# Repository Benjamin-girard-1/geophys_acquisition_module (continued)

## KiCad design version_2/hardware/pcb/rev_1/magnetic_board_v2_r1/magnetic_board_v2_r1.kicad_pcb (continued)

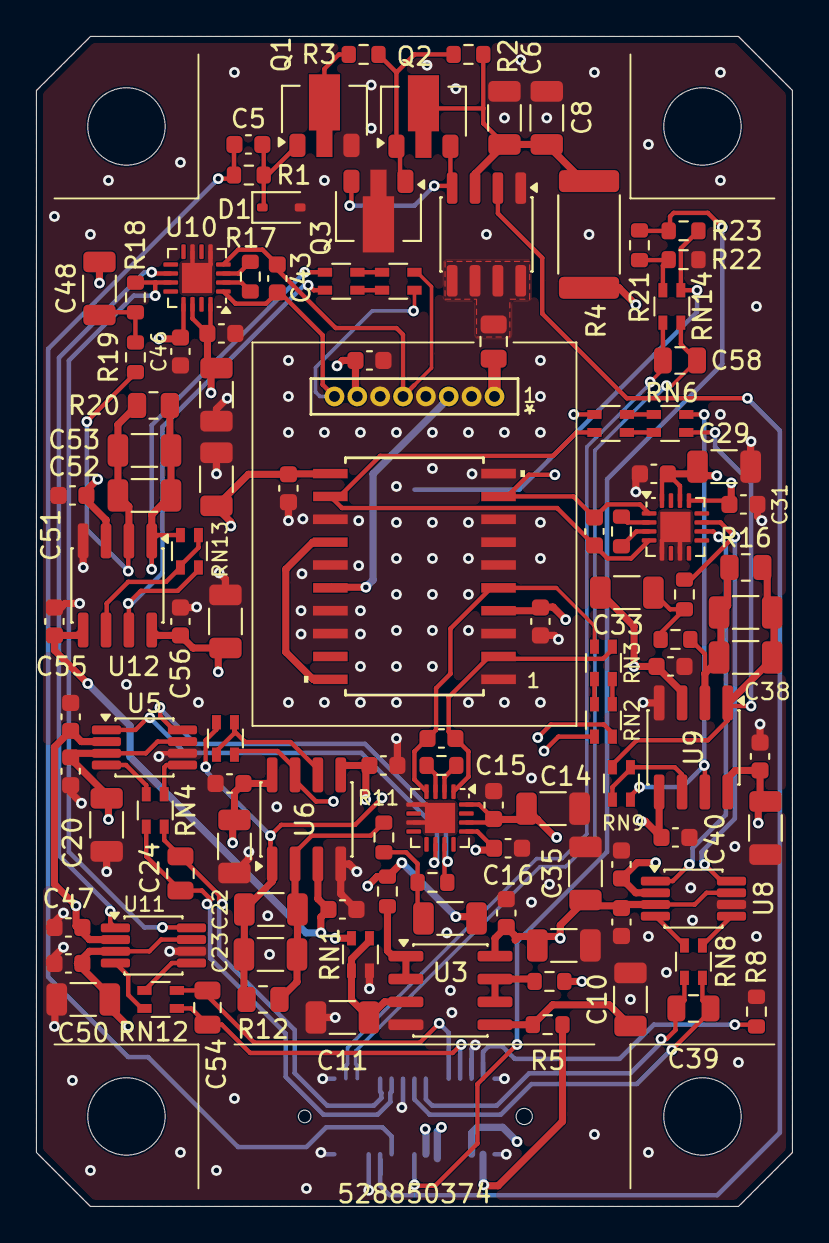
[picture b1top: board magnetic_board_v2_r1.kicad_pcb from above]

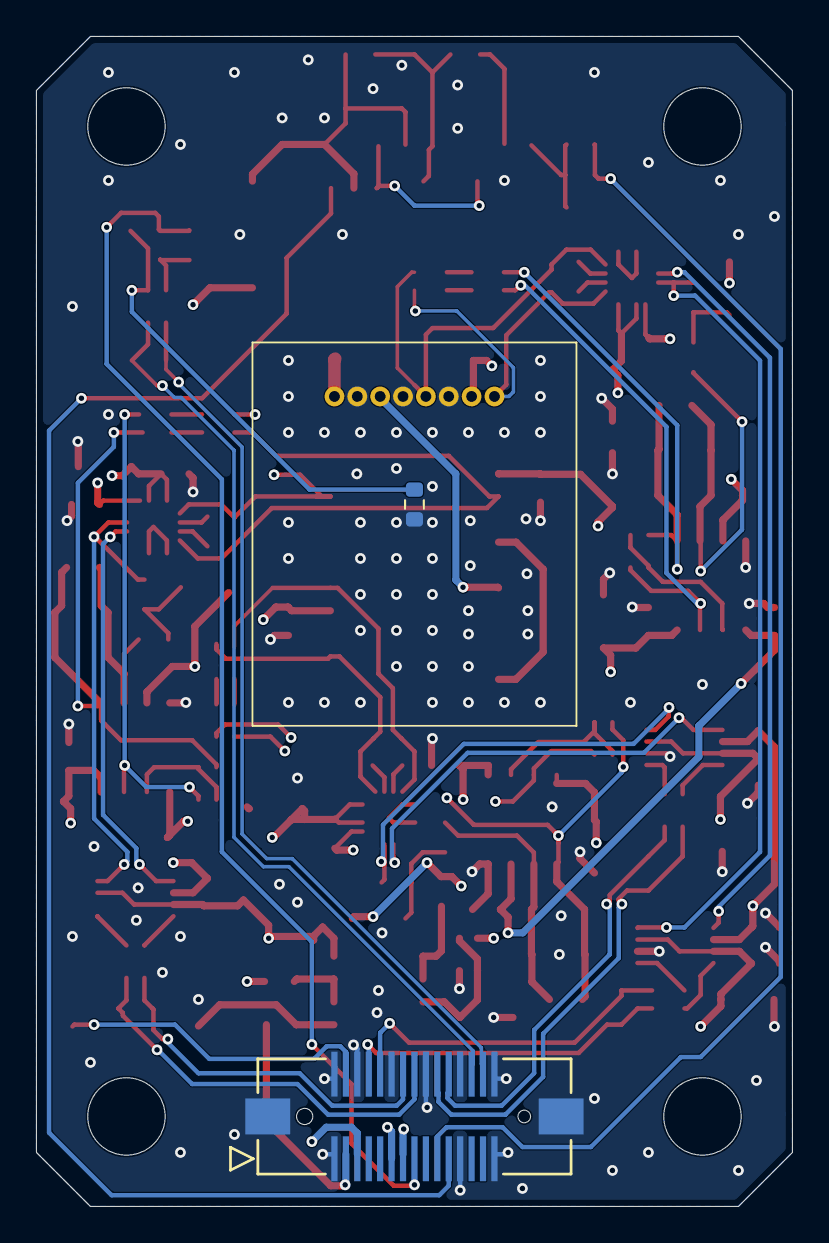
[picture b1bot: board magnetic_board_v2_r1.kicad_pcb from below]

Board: 4 copper layers, 42.0 x 65.0 mm, 118 parts (2 on the bottom side), 79 nets.

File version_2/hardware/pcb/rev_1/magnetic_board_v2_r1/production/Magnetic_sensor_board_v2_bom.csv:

Designator,Footprint,Quantity,Value,LCSC Part #
"C1, C6, C8",1206,3,10u,C13585
"C10, C11, C12, C14, C20, C22, C23, C27, C29, C35, C37, C38, C42, C44, C50, C52, C53, C57",1206,18,4u7,C29823
"C13, C28, C43",0603,3,10n,C57112
"C15, C16, C17, C19, C2, C21, C25, C26, C3, C30, C31, C32, C34, C36, C4, C40, C41, C45, C46, C47, C49, C51, C55, C56, C9",0603,25,100n,C14663
"C18, C33, C48",1206,3,47u,C96123
"C24, C39, C54, C58, C7",0805,5,220n,C5378
C5,0603,1,1n,C1588
D1,D_SOD-323,1,1N4148WS,C2128
"Q1, Q2",SOT-89-3,2,D882,C9634
Q3,SOT-89-3,1,B772,C24278
Q4,SO-8_3.9x4.9mm_P1.27mm,1,DMC3028LSD,C460874
"R1, R2, R3, R5",0603,4,1k,C21190
"R10, R14, R18",0603,3,300k,C5948140
"R11, R15, R19, R8",0603,4,20k,C2076520
"R12, R16, R20",0805,3,100M,C169373
"R13, R17, R9",0603,3,120,C860088
"R21, R22, R23",0603,3,100k,C860056
R4,2512,1,220,C4202072
"R6, R7",0603,2,20,C22950
RN1,R_Array_Convex_2x0603,1,10k,C2654064
"RN10, RN11, RN13, RN2, RN3, RN5, RN6, RN7, RN9",R_Array_Convex_2x0603,9,20k,C5553154
"RN12, RN14, RN4, RN8",R_Array_Convex_2x0603,4,1k,C1731140
"U10, U4, U7",VQFN-16-1EP_3x3mm_P0.5mm_EP1.68x1.68mm,3,INA851RGTR,C5371575
"U11, U5, U8",VSSOP-8_3x3mm_P0.65mm,3,THP210DGK,C976185
"U12, U3, U6, U9",SOIC-8_3.9x4.9mm_P1.27mm,4,OPA2197xD,C139363

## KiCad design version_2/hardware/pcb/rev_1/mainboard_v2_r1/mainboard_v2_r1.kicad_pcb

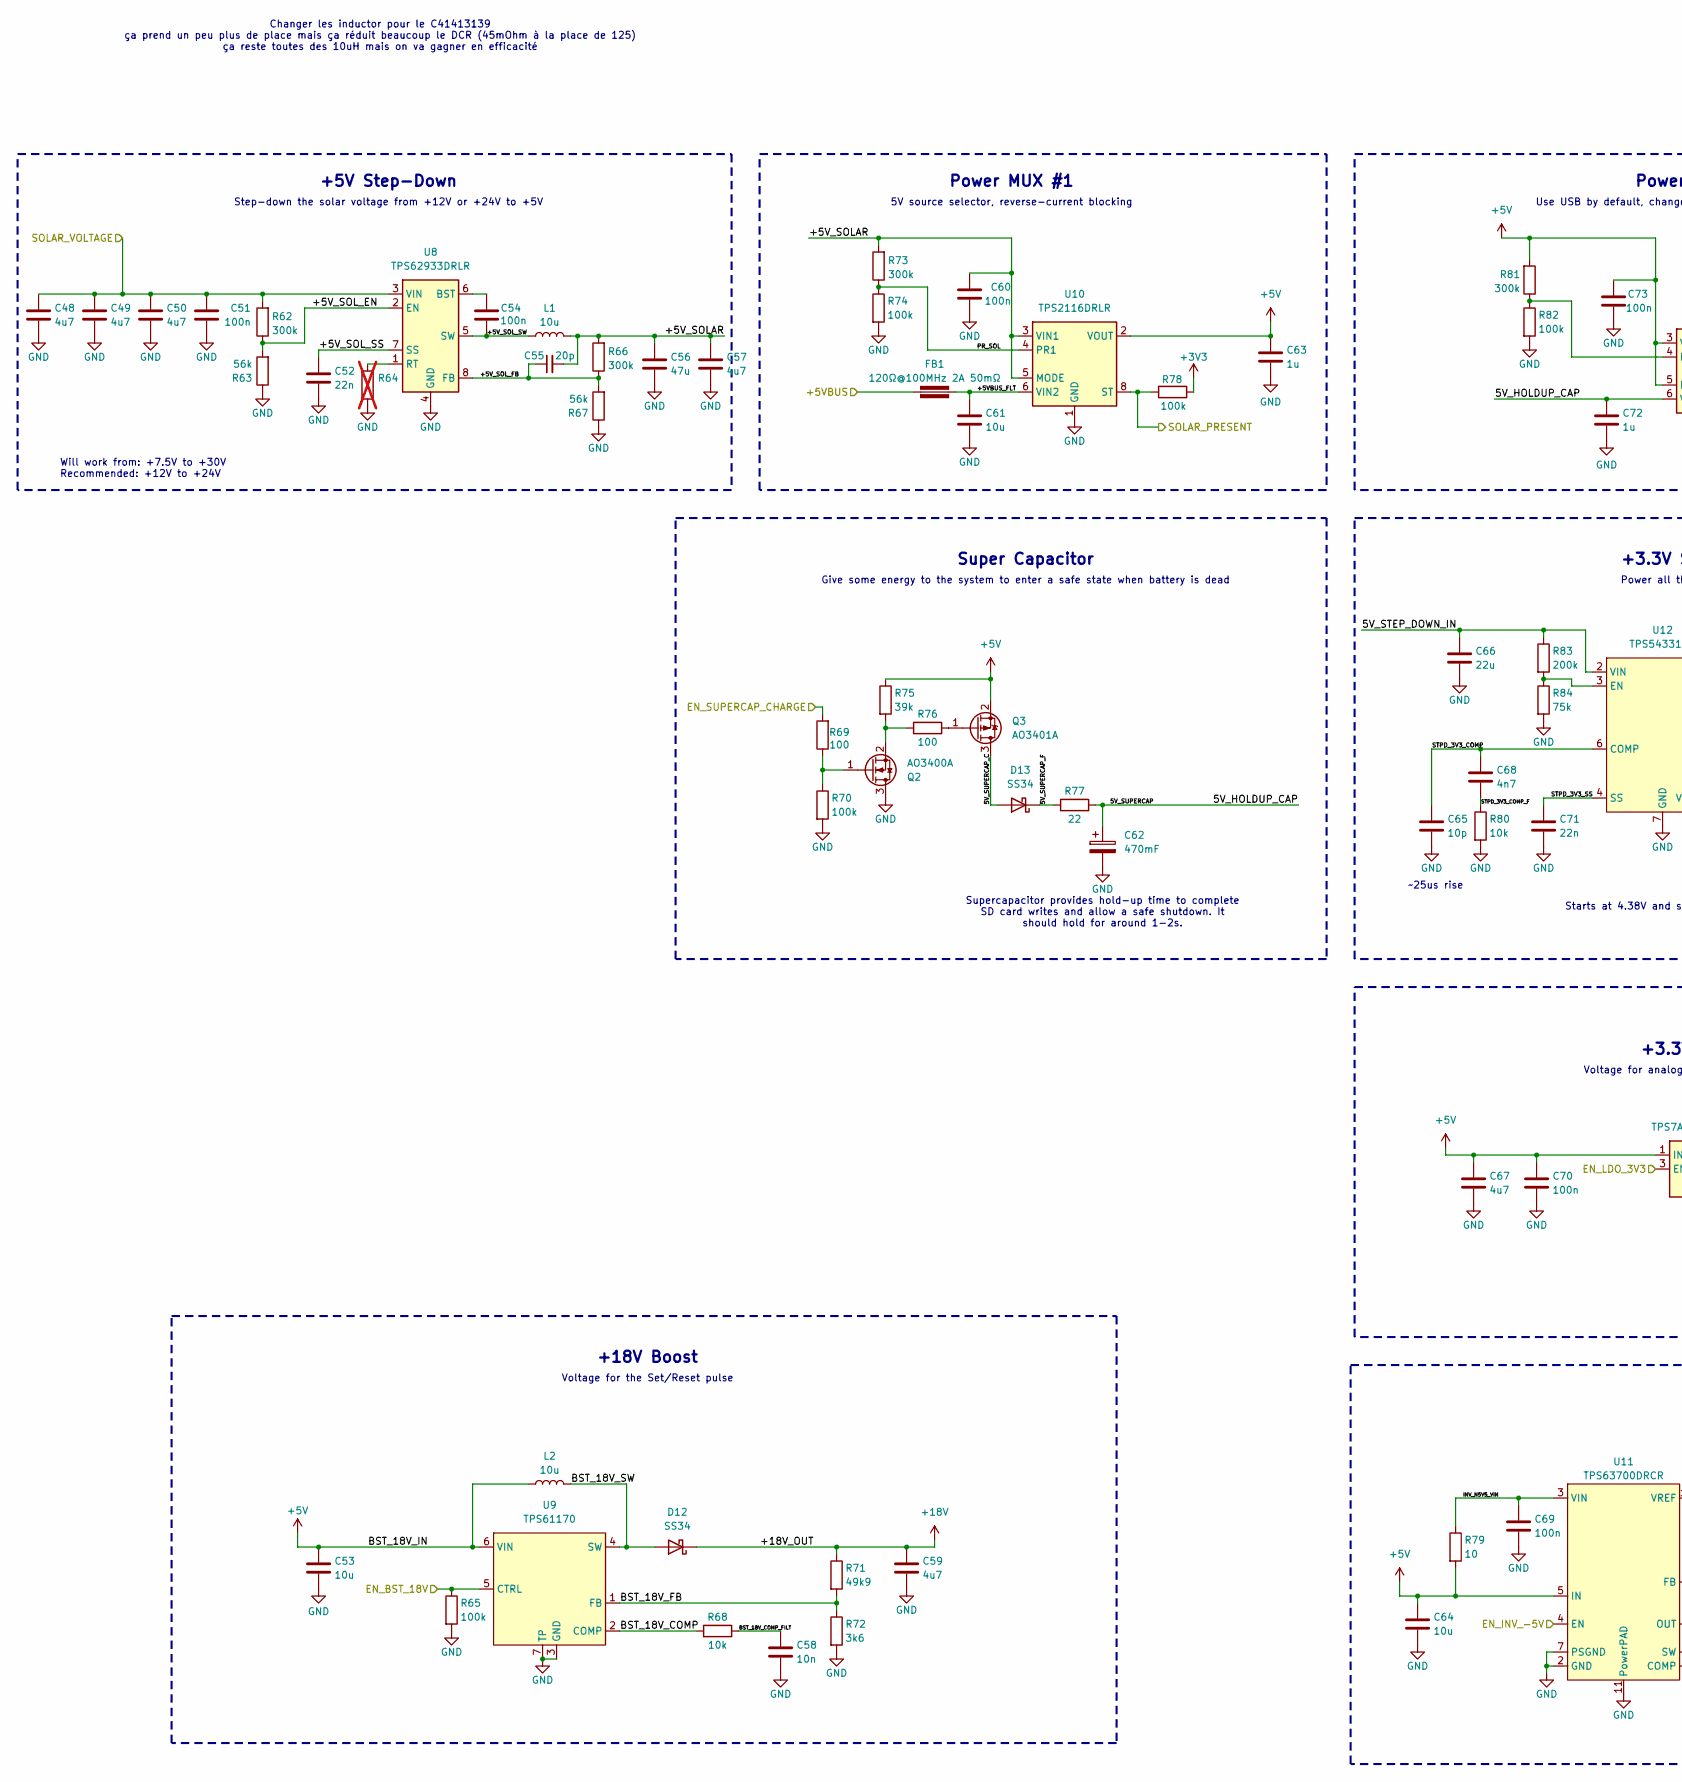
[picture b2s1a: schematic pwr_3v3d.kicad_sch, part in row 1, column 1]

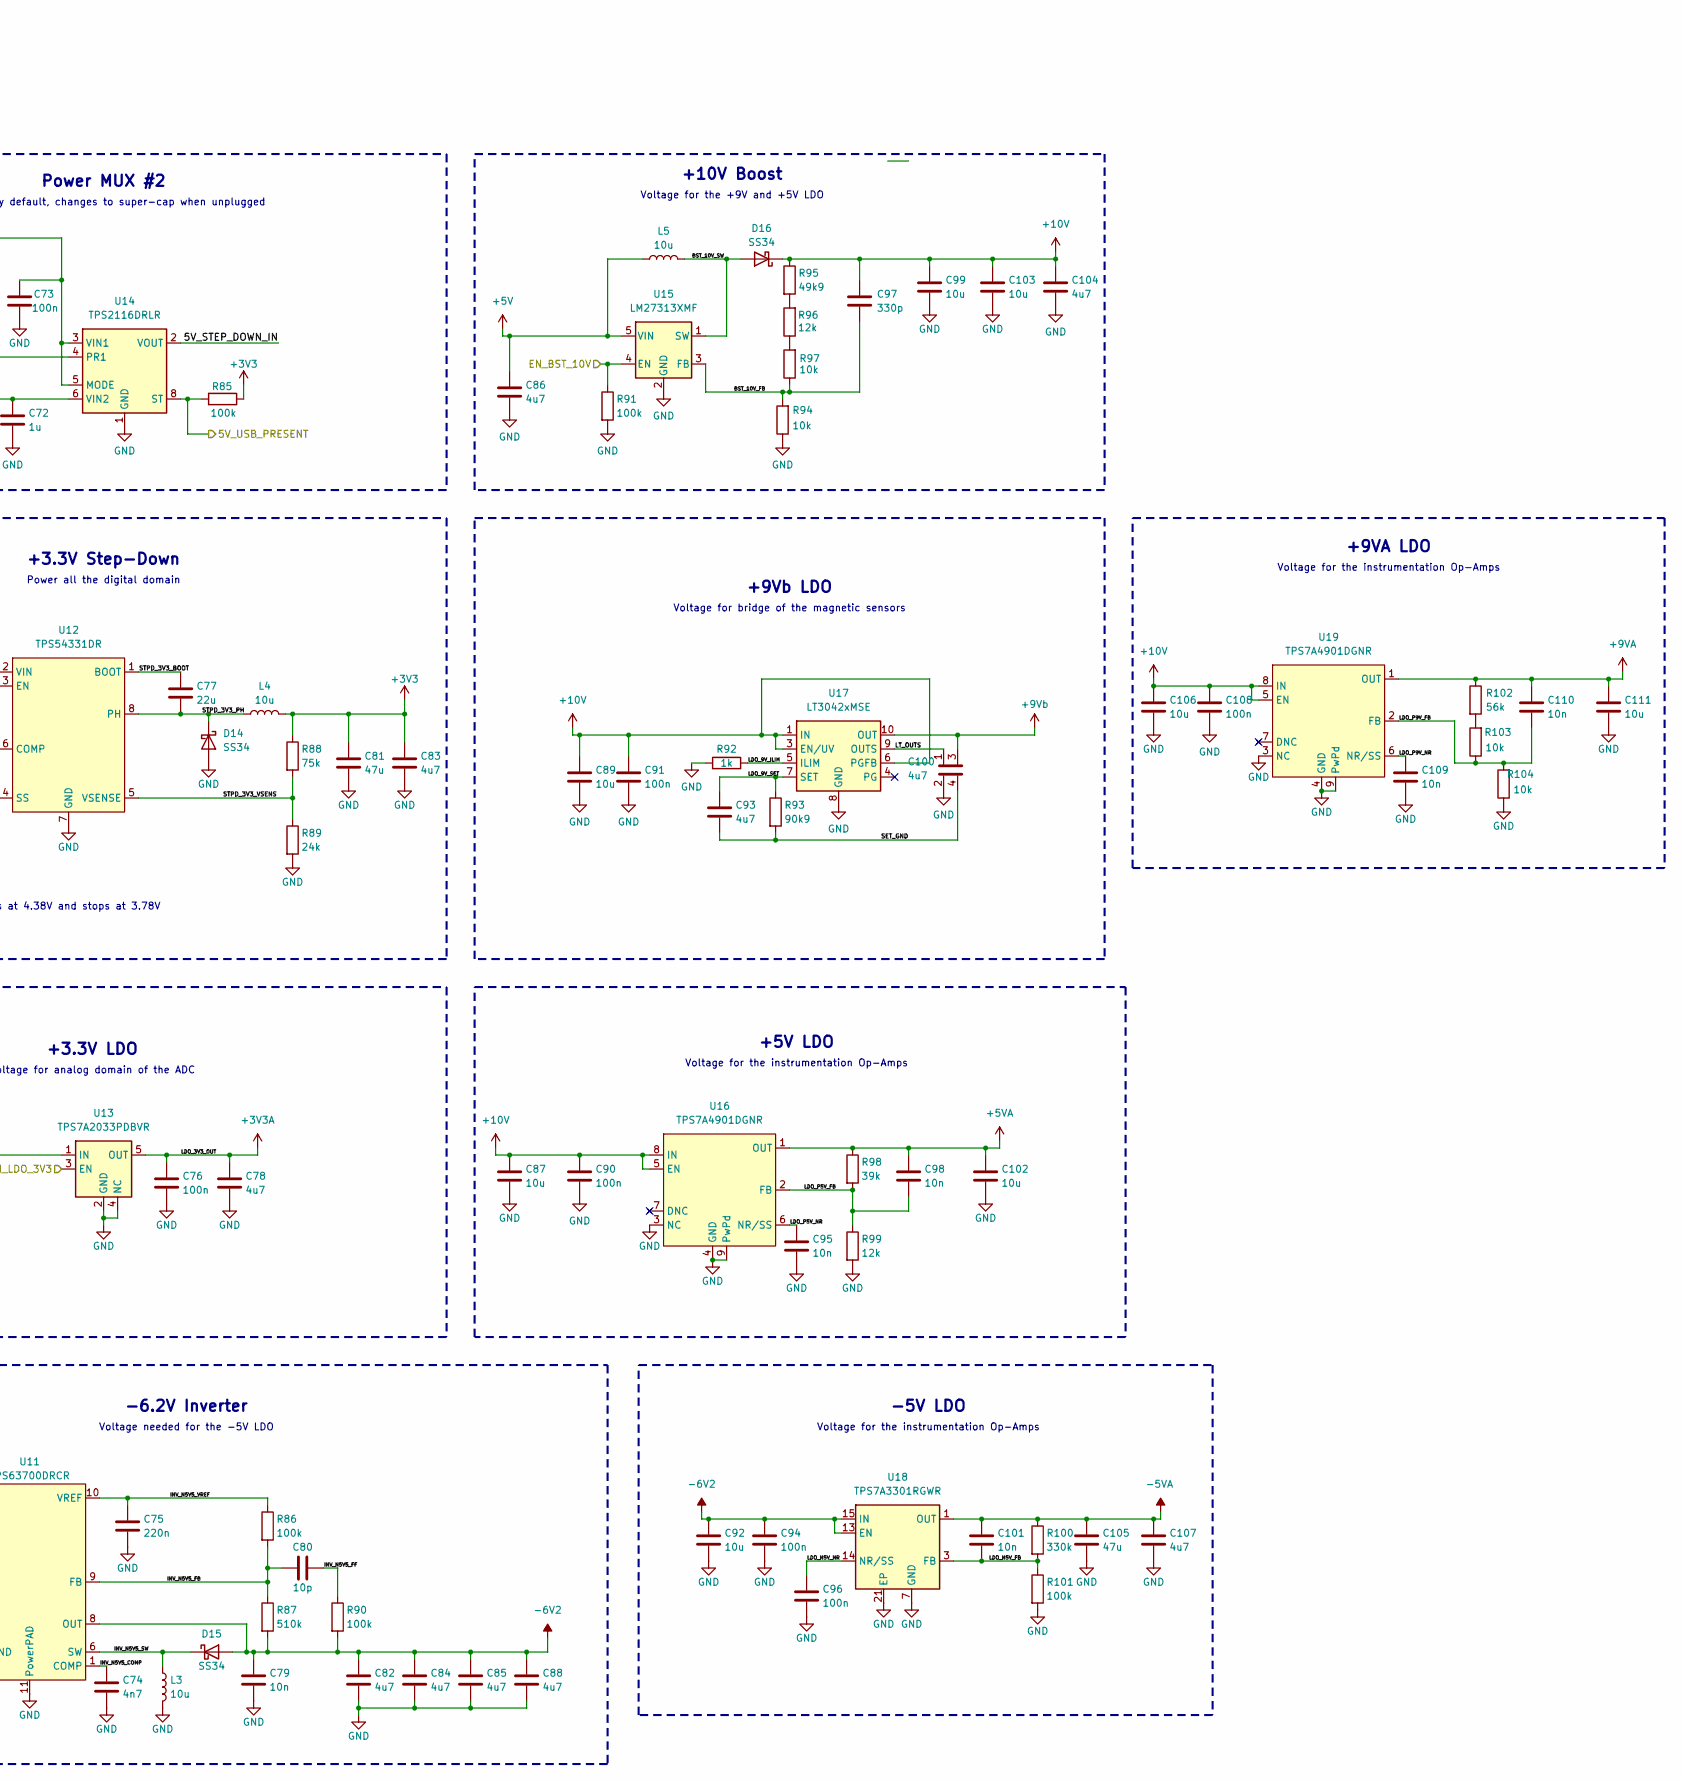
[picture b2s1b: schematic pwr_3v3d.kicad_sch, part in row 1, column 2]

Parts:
C48, C49, C50, C57, C59, C67, C78, C82, C83, C84, C85, C86, C88, C93, C104, C107: 4u7; C_1206_3216Metric; LCSC C29823
C51, C54, C60, C69, C70, C73, C76, C90, C91, C94, C96, C108: 100n; C_0603_1608Metric; LCSC C14663
C52, C71: 22n; C_0603_1608Metric; LCSC C21122
C53, C61, C64, C87, C89, C92, C99, C102, C103, C106, C111: 10u; C_0805_2012Metric; LCSC C15850
C55: 20p; C_0402_1005Metric; LCSC C1554
C56, C81, C105: 47u; C_1206_3216Metric; LCSC C96123
C58, C79, C95, C98, C101, C109, C110: 10n; C_0603_1608Metric; LCSC C57112
C62: 470mF; C_Radial_D8.0mm_P11.50mm
C63, C72: 1u; C_0805_2012Metric; LCSC C28323
C65, C80: 10p; C_0603_1608Metric; LCSC C1634
C66, C77: 22u; C_1206_3216Metric; LCSC C12891
C68, C74: 4n7; C_0603_1608Metric; LCSC C53987
C75: 220n; C_0603_1608Metric; LCSC C21120
C97: 330p; C_0603_1608Metric; LCSC C1664
C100: 4u7; kelvin_connect_1206_SMD_CAP; LCSC C29823
D12, D13, D14, D15, D16: SS34; D_SMA; LCSC C8678
FB1: 120Ω@100MHz 2A 50mΩ; L_0603_1608Metric; LCSC C14709
L1, L2, L3, L4, L5: 10u; L_Sunlord_MWSA0503S; LCSC C177248
Q2: AO3400A; SOT-23; LCSC C20917
Q3: AO3401A; SOT-23; LCSC C15127
R62, R66, R73, R81: 300k; R_0603_1608Metric; LCSC C23024
R63, R67, R102: 56k; R_0603_1608Metric; LCSC C23206
R64: R_0603_1608Metric; not fitted
R65, R70, R74, R78, R82, R85, R86, R90, R91, R101: 100k; R_0603_1608Metric; LCSC C25803
R68, R80, R94, R97, R103, R104: 10k; R_0603_1608Metric; LCSC C25804
R69, R76: 100; R_0805_2012Metric; LCSC C17408
R71, R95: 49k9; R_0603_1608Metric; LCSC C23184
R72: 3k6; R_0603_1608Metric; LCSC C22980
R75, R98: 39k; R_0603_1608Metric; LCSC C23153
R77: 22; R_2512_6332Metric; LCSC C2974113
R79: 10; R_0603_1608Metric; LCSC C22859
R83: 200k; R_0603_1608Metric; LCSC C25811
R84, R88: 75k; R_0603_1608Metric; LCSC C23242
R87: 510k; R_0603_1608Metric; LCSC C23192
R89: 24k; R_0603_1608Metric; LCSC C23352
R92: 1k; R_0603_1608Metric; LCSC C21190
R93: 90k9; R_1206_3216Metric; LCSC C870933
R96, R99: 12k; R_0603_1608Metric; LCSC C22790
R100: 330k; R_0603_1608Metric; LCSC C23137
U8: TPS62933DRLR; SOT-583-8; LCSC C3200405
U9: TPS61170; WSON-6-1EP_2x2mm_P0.65mm_EP1x1.6mm; LCSC C15163
U10, U14: TPS2116DRLR; SOT-583-8; LCSC C3235557
U11: TPS63700DRCR; VSON-10-1EP_3x3mm_P0.5mm_EP1.2x2mm; LCSC C54792
U12: TPS54331DR; SOIC-8_3.9x4.9mm_P1.27mm; LCSC C9865
U13: TPS7A2033PDBVR; SOT-23-5; LCSC C2862740
U15: LM27313XMF; SOT-23-5; LCSC C341750
U16, U19: TPS7A4901DGNR; HVSSOP-8-1EP_3x3mm_P0.65mm_EP1.57x1.89mm; LCSC C16430
U17: LT3042xMSE; MSOP-10-1EP_3x3mm_P0.5mm_EP1.68x1.88mm; LCSC C461518
U18: TPS7A3301RGWR; Texas_RGW0020A_VQFN-20-1EP_5x5mm_P0.65mm_EP3.15x3.15mm; LCSC C90082

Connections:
+3V3: C81.1, C83.1, L4.2, R78.1, R85.1, R88.1; also elsewhere on the board
+3V3A: C76.1, C78.1, U13.5 (OUT); also elsewhere on the board
+5V: C53.1, C63.1, C64.1, C67.1, C70.1, C73.2, C86.1, L2.1, L5.1, Q3.2, R75.1, R79.2, R81.2, U9.6 (VIN), U10.2 (VOUT), U10.7 (VOUT), U11.5 (IN), U13.1 (IN), U14.3 (VIN1), U14.5 (MODE), U15.5 (VIN)
+5VA: C98.1, C102.1, R98.1, U16.1 (OUT); also elsewhere on the board
+9VA: C110.1, C111.1, R102.1, U19.1 (OUT); also elsewhere on the board
+9Vb: C100.3, U17.10 (OUT); also elsewhere on the board
+10V: C87.1, C89.1, C90.1, C91.1, C97.1, C99.1, C103.1, C104.1, C106.1, C108.1, D16.1 (K), R95.1, U16.5 (EN), U16.8 (IN), U17.1 (IN), U17.2 (IN), U17.3 (EN/UV), U17.6 (PGFB), U19.5 (EN), U19.8 (IN)
+18V: C59.1, D12.1 (K), R71.1; also elsewhere on the board
-5VA: C101.1, C105.1, C107.1, R100.1, U18.1 (OUT), U18.20 (OUT); also elsewhere on the board
-6V2: C79.1, C82.1, C84.1, C85.1, C88.1, C92.1, C94.1, D15.2 (A), R87.2, R90.2, U11.8 (OUT), U18.13 (EN), U18.15 (IN), U18.16 (IN)
/DATA_SAVING/+5VBUS: FB1.1; also elsewhere on the board
/IO_CONNECTOR/SOLAR_VOLTAGE: C48.1, C49.1, C50.1, C51.2, R62.2, U8.3 (VIN); also elsewhere on the board
/MCU_ESP32S3/5V_USB_PRESENT: R85.2, U14.8 (ST); also elsewhere on the board
/MCU_ESP32S3/EN_BST_10V: R91.1, U15.4 (EN); also elsewhere on the board
/MCU_ESP32S3/EN_BST_18V: R65.1, U9.5 (CTRL); also elsewhere on the board
/MCU_ESP32S3/EN_INV_-5V: U11.4 (EN); also elsewhere on the board
/MCU_ESP32S3/EN_LDO_3V3: U13.3 (EN); also elsewhere on the board
/MCU_ESP32S3/EN_SUPERCAP_CHARGE: R69.2; also elsewhere on the board
/MCU_ESP32S3/SOLAR_PRESENT: R78.2, U10.8 (ST); also elsewhere on the board
/POWER/5V_HOLDUP_CAP: C62.1, C72.1, R77.2, U14.6 (VIN2)
/POWER/5V_STEP_DOWN_IN: C66.1, R83.1, U12.2 (VIN), U14.2 (VOUT), U14.7 (VOUT)
/POWER/5V_SUPERCAP_C: D13.2 (A), Q3.3
/POWER/5V_SUPERCAP_F: D13.1 (K), R77.1
/POWER/+5VBUS_FLT: C61.1, FB1.2, U10.6 (VIN2)
/POWER/+5V_SOLAR: C55.2, C56.1, C57.1, C60.2, L1.2, R66.2, R73.2, U10.3 (VIN1), U10.5 (MODE)
/POWER/+5V_SOL_EN: R62.1, R63.2, U8.2 (EN)
/POWER/+5V_SOL_FB: C55.1, R66.1, R67.2, U8.8 (FB)
/POWER/+5V_SOL_SS: C52.1, U8.7 (SS)
/POWER/+5V_SOL_SW: C54.1, L1.1, U8.5 (SW)
/POWER/BST_10V_FB: C97.2, R94.2, R97.1, U15.3 (FB)
/POWER/BST_10V_SW: D16.2 (A), L5.2, U15.1 (SW)
/POWER/BST_18V_COMP: R68.1, U9.2 (COMP)
/POWER/BST_18V_COMP_FILT: C58.1, R68.2
/POWER/BST_18V_FB: R71.2, R72.1, U9.1 (FB)
/POWER/BST_18V_SW: D12.2 (A), L2.2, U9.4 (SW)
/POWER/INV_N5V5_COMP: C74.1, U11.1 (COMP)
/POWER/INV_N5V5_FB: C80.1, R86.2, R87.1, U11.9 (FB)
/POWER/INV_N5V5_FF: C80.2, R90.1
/POWER/INV_N5V5_SW: D15.1 (K), L3.1, U11.6 (SW)
/POWER/INV_N5V5_VIN: C69.1, R79.1, U11.3 (VIN)
/POWER/INV_N5V5_VREF: C75.1, R86.1, U11.10 (VREF)
/POWER/LDO_9V_ILIM: R92.2, U17.5 (ILIM)
/POWER/LDO_9V_SET: C93.1, R93.1, U17.7 (SET)
/POWER/LDO_N5V_FB: C101.2, R100.2, R101.1, U18.3 (FB)
/POWER/LDO_N5V_NR: C96.1, U18.14 (NR/SS)
/POWER/LDO_P5V_FB: C98.2, R98.2, R99.1, U16.2 (FB)
/POWER/LDO_P5V_NR: C95.1, U16.6 (NR/SS)
/POWER/LDO_P9V_FB: C110.2, R103.1, R104.2, U19.2 (FB)
/POWER/LDO_P9V_NR: C109.1, U19.6 (NR/SS)
/POWER/LT_OUTS: C100.1, U17.9 (OUTS)
/POWER/PR_SOL: R73.1, R74.1, U10.4 (PR1)
/POWER/SET_GND: C93.2, C100.4, R93.2
/POWER/STPD_3V3_BOOT: C77.1, U12.1 (BOOT)
/POWER/STPD_3V3_COMP: C65.1, C68.1, U12.6 (COMP)
/POWER/STPD_3V3_COMP_F: C68.2, R80.1
/POWER/STPD_3V3_PH: C77.2, D14.1 (K), L4.1, U12.8 (PH)
/POWER/STPD_3V3_SS: C71.1, U12.4 (SS)
/POWER/STPD_3V3_VSENS: R88.2, R89.1, U12.5 (VSENSE)
GND: C48.2, C49.2, C50.2, C51.1, C52.2, C53.2, C56.2, C57.2, C58.2, C59.2, C60.1, C61.2, C62.2, C63.2, C64.2, C65.2, C66.2, C67.2, C69.2, C70.2, C71.2, C72.2, C73.1, C74.2, C75.2, C76.2, C78.2, C79.2, C81.2, C82.2, C83.2, C84.2, C85.2, C86.2, C87.2, C88.2, C89.2, C90.2, C91.2, C92.2, C94.2, C95.2, C96.2, C99.2, C100.2, C102.2, C103.2, C104.2, C105.2, C106.2, C107.2, C108.2, C109.2, C111.2, D14.2 (A), L3.2, Q2.3 (D), R63.1, R64.2, R65.2, R67.1, R70.2, R72.2, R74.2, R80.2, R82.2, R84.2, R89.2, R91.2, R92.1, R94.1, R99.2, R101.2, R104.1, U8.4 (GND), U9.3 (GND), U9.7 (TP), U10.1 (GND), U11.2 (GND), U11.7 (PSGND), U11.11 (PowerPAD), U12.7 (GND), U13.2 (GND), U13.4 (NC), U14.1 (GND), U15.2 (GND), U16.3 (NC), U16.4 (GND), U16.9 (PwPd), U17.8 (GND), U17.11 (GND), U18.7 (GND), U18.21 (EP), U19.3 (NC), U19.4 (GND), U19.9 (PwPd); also elsewhere on the board
unnamed: Q2.1 (G), R69.1, R70.1
unnamed: Q2.2 (S), R75.2, R76.1
unnamed: Q3.1, R76.2
unnamed: R95.2, R96.2
unnamed: R96.1, R97.2
unnamed: R102.2, R103.2
unnamed: C54.2, U8.6 (BST)
unnamed: R64.1, U8.1 (RT)
unnamed: R83.2, R84.1, U12.3 (EN)
unnamed: R81.1, R82.1, U14.4 (PR1)

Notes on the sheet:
Changer les inductor pour le C41413139 ça prend un peu plus de place mais ça réduit beaucoup le DCR (45mOhm à la place de 125) ça reste toutes des 10uH mais on va gagner en efficacité
Voltage for the instrumentation Op-Amps
-6.2V Inverter
+5V Step-Down
5V source selector, reverse-current blocking
Use USB by default, changes to super-cap when unplugged
~25us rise
Voltage for the +9V and +5V LDO
Super Capacitor
Voltage for analog domain of the ADC
+5V LDO
+3.3V LDO
Voltage needed for the -5V LDO
+10V Boost
Give some energy to the system to enter a safe state when battery is dead
Power MUX #1
+3.3V Step-Down
+9VA LDO
+9Vb LDO
Step-down the solar voltage from +12V or +24V to +5V
Power all the digital domain
+18V Boost
Starts at 4.38V and stops at 3.78V
Supercapacitor provides hold-up time to complete SD card writes and allow a safe shutdown. It should hold for around 1-2s.
Will work from: +7.5V to +30V Recommended: +12V to +24V
-5V LDO
Voltage for bridge of the magnetic sensors
Power MUX #2
Voltage for the Set/Reset pulse

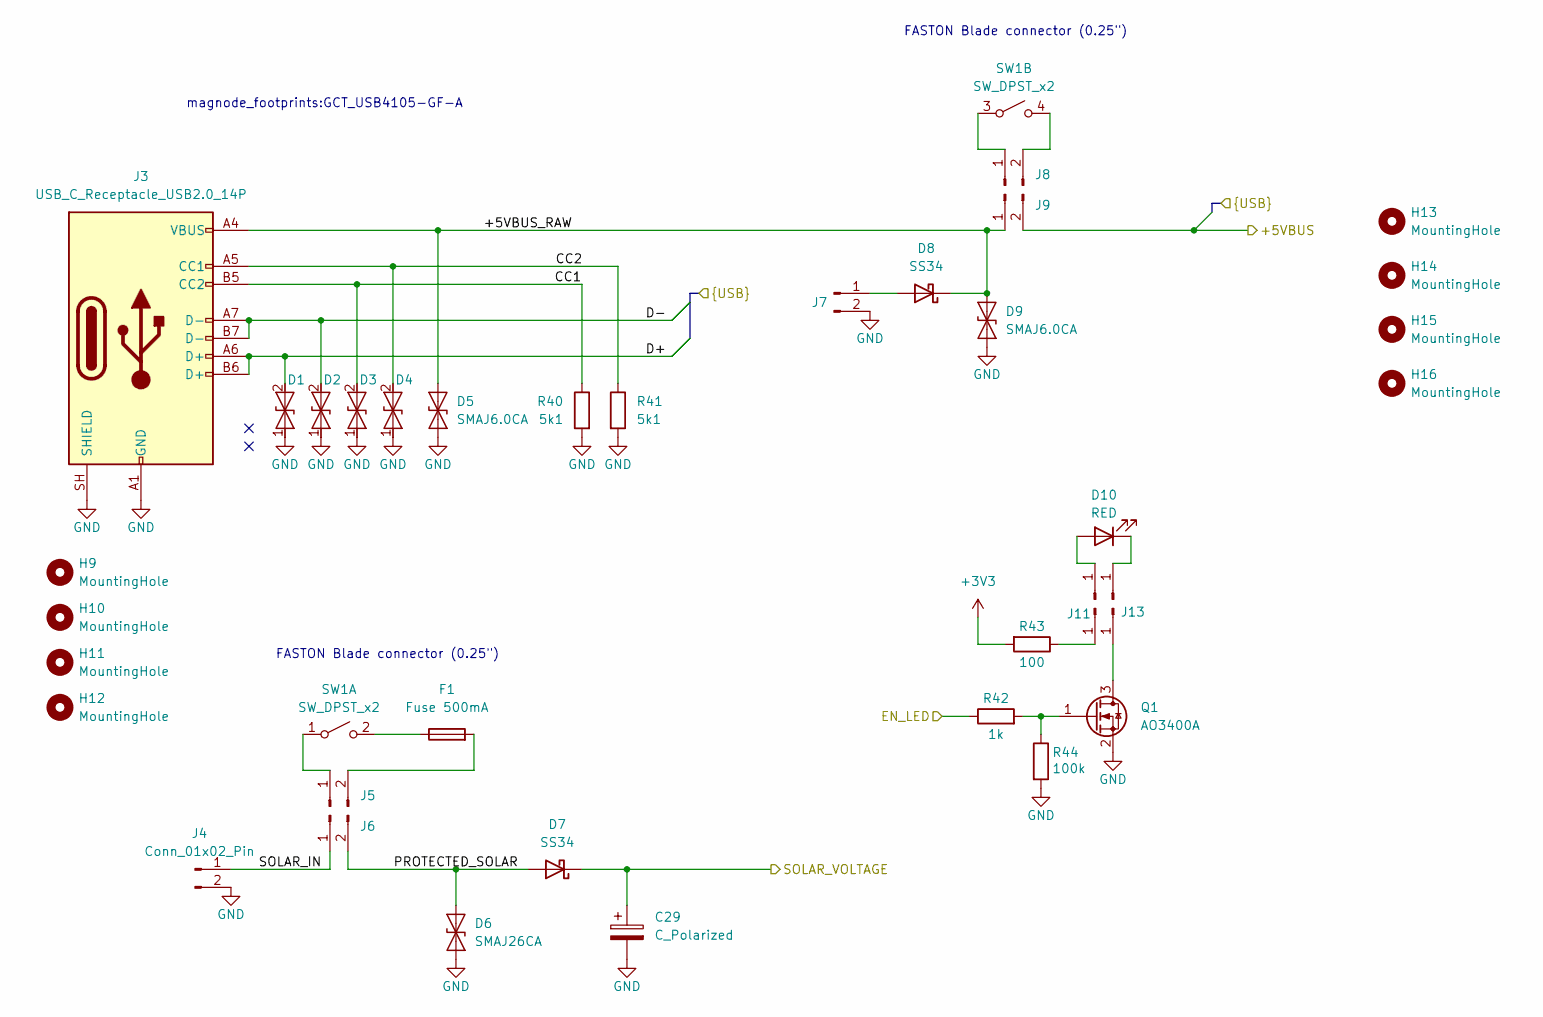
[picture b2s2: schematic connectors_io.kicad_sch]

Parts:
C29: C_Polarized; CP_Radial_D10.0mm_P5.00mm
D1, D2, D3, D4: H5VUD5BB; D_SOD-523; LCSC C20615820
D5: SMAJ6.0CA; D_SMA
D6: SMAJ26CA; D_SMA; LCSC SMAJ26CA
D7, D8: SS34; D_SMA; LCSC C8678
D9: SMAJ6.0CA; D_SMA; LCSC C19077526
D10: RED
F1: Fuse 500mA
H9, H10, H11, H12, H13, H14, H15, H16: MountingHole; MountingHole_4.3mm_M4
J3: USB_C_Receptacle_USB2.0_14P; AMPHENOL_12402054M611A
J4, J6, J7, J9: Conn_01x02_Pin; KEYSTONE_7817
J5, J8: Conn_01x02_Pin
J10, J12: Conn_01x01_Pin
J11, J13: Conn_01x01_Pin; KEYSTONE_1267
Q1: AO3400A; SOT-23; LCSC C20917
R40, R41: 5k1; R_0603_1608Metric; LCSC C23186
R42: 1k; R_0603_1608Metric; LCSC C21190
R43: 100; R_0805_2012Metric; LCSC C17408
R44: 100k; R_0603_1608Metric; LCSC C25803
SW1: SW_DPST_x2

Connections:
+3V3: R43.2; also elsewhere on the board
/DATA_SAVING/+5VBUS: J9.2; also elsewhere on the board
/DATA_SAVING/CC1: D3.2, J3.B5 (CC2), R40.1
/DATA_SAVING/CC2: D4.2, J3.A5 (CC1), R41.1
/DATA_SAVING/D+: D1.2, J3.A6 (D+), J3.B6 (D+); also elsewhere on the board
/DATA_SAVING/D-: D2.2, J3.A7 (D-), J3.B7 (D-); also elsewhere on the board
/IO_CONNECTOR/+5VBUS_RAW: D5.2 (A2), D8.1 (K), D9.2 (A2), J3.A4 (VBUS), J3.A9 (VBUS), J3.B4 (VBUS), J3.B9 (VBUS), J9.1
/IO_CONNECTOR/EN_LED: R42.1; also elsewhere on the board
/IO_CONNECTOR/PROTECTED_SOLAR: D6.2 (A2), D7.2 (A), J6.2
/IO_CONNECTOR/SOLAR_IN: J4.1, J6.1
/IO_CONNECTOR/SOLAR_VOLTAGE: C29.1, D7.1 (K); also elsewhere on the board
GND: C29.2, D1.1, D2.1, D3.1, D4.1, D5.1 (A1), D6.1 (A1), D9.1 (A1), J3.A1 (GND), J3.A12 (GND), J3.B1 (GND), J3.B12 (GND), J3.SH (SHIELD), J4.2, J7.2, Q1.2 (S), R40.2, R41.2, R44.2; also elsewhere on the board
unnamed: D8.2 (A), J7.1
unnamed: D10.1 (K), J12.1
unnamed: D10.2 (A), J10.1
unnamed: F1.1, SW1.2 (B)
unnamed: F1.2, J5.2
unnamed: J5.1, SW1.1 (A)
unnamed: J8.1, SW1.3 (A)
unnamed: J8.2, SW1.4 (B)
unnamed: J11.1 (Pin_1_1), R43.1
unnamed: J13.1 (Pin_1_1), Q1.3 (D)
unnamed: Q1.1 (G), R42.2, R44.1

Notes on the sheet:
FASTON Blade connector (0.25")
magnode_footprints:GCT_USB4105-GF-A

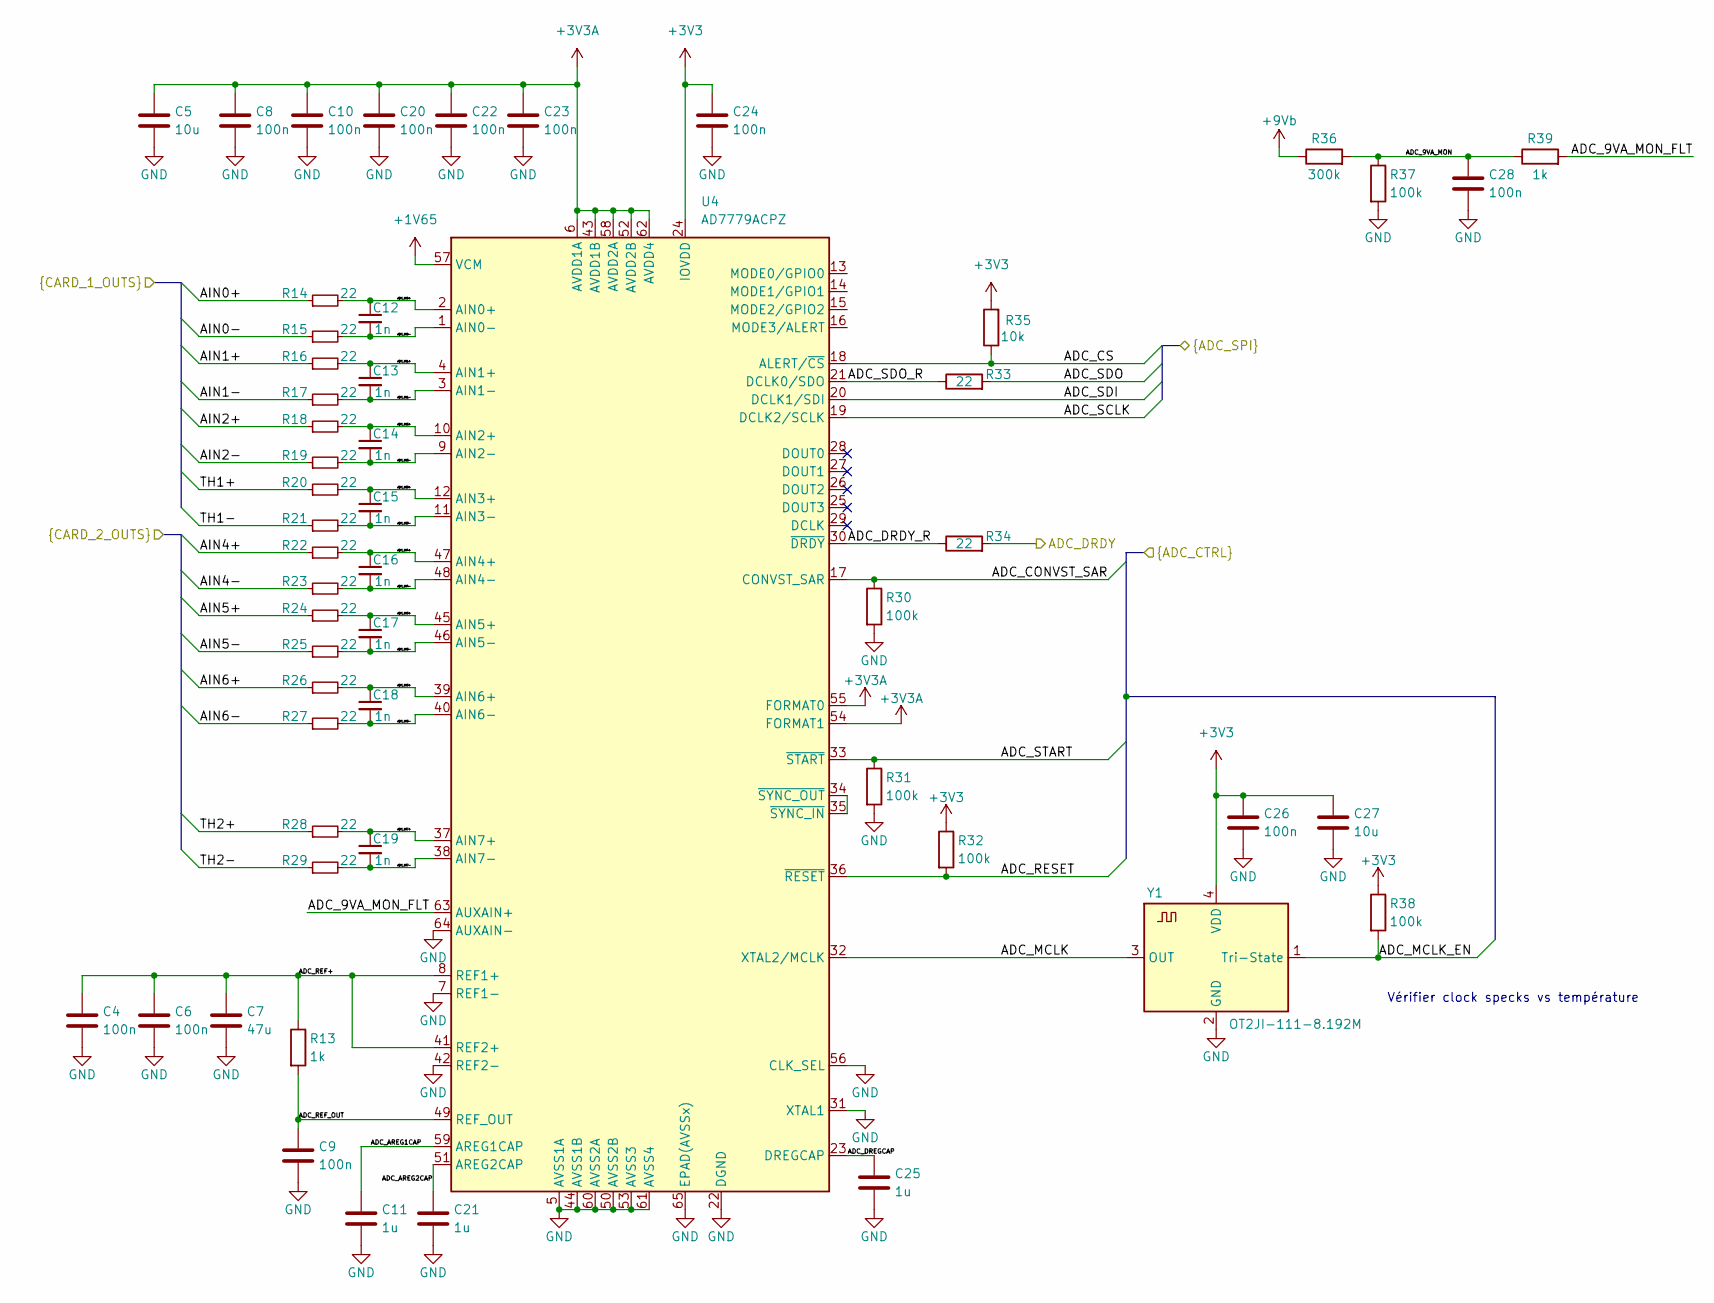
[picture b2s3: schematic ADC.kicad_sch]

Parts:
C4, C6, C8, C9, C10, C20, C22, C23, C24, C26, C28: 100n; C_0603_1608Metric; LCSC C14663
C5, C27: 10u; C_0805_2012Metric; LCSC C15850
C7: 47u; C_1206_3216Metric; LCSC C96123
C11, C21, C25: 1u; C_0805_2012Metric; LCSC C28323
C12, C13, C14, C15, C16, C17, C18, C19: 1n; C_0603_1608Metric; LCSC C1588
R13, R39: 1k; R_0603_1608Metric; LCSC C21190
R14, R15, R16, R17, R18, R19, R20, R21, R22, R23, R24, R25, R26, R27, R28, R29, R33, R34: 22; R_0603_1608Metric; LCSC C23345
R30, R31, R32, R37, R38: 100k; R_0603_1608Metric; LCSC C25803
R35: 10k; R_0603_1608Metric; LCSC C25804
R36: 300k; R_0603_1608Metric; LCSC C23024
U4: AD7779ACPZ; QFN-64-1EP_9x9mm_P0.5mm_EP7.65x7.65mm; LCSC C398822
Y1: OT2JI-111-8.192M; Crystal_SMD_3225-4Pin_3.2x2.5mm; LCSC C7425393

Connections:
+1V65: U4.57 (VCM); also elsewhere on the board
+3V3: C24.1, C26.1, C27.1, R32.1, R35.2, R38.1, U4.24 (IOVDD), Y1.4 (VDD); also elsewhere on the board
+3V3A: C5.1, C8.1, C10.1, C20.1, C22.1, C23.1, U4.6 (AVDD1A), U4.43 (AVDD1B), U4.52 (AVDD2B), U4.54 (FORMAT1), U4.55 (FORMAT0), U4.58 (AVDD2A), U4.62 (AVDD4); also elsewhere on the board
+9Vb: R36.1; also elsewhere on the board
/ADC_AD777x/ADC_9VA_MON: C28.1, R36.2, R37.1, R39.1
/ADC_AD777x/ADC_9VA_MON_FLT: R39.2, U4.63 (AUXAIN+)
/ADC_AD777x/ADC_AREG1CAP: C11.1, U4.59 (AREG1CAP)
/ADC_AD777x/ADC_AREG2CAP: C21.1, U4.51 (AREG2CAP)
/ADC_AD777x/ADC_CONVST_SAR: R30.1, U4.17 (CONVST_SAR); also elsewhere on the board
/ADC_AD777x/ADC_CS: R35.1, U4.18 (ALERT/~CS); also elsewhere on the board
/ADC_AD777x/ADC_DRDY: R34.2; also elsewhere on the board
/ADC_AD777x/ADC_DRDY_R: R34.1, U4.30 (~DRDY)
/ADC_AD777x/ADC_DREGCAP: C25.1, U4.23 (DREGCAP)
/ADC_AD777x/ADC_IN0+: C12.1, R14.2, U4.2 (AIN0+)
/ADC_AD777x/ADC_IN0-: C12.2, R15.2, U4.1 (AIN0-)
/ADC_AD777x/ADC_IN1+: C13.1, R16.2, U4.4 (AIN1+)
/ADC_AD777x/ADC_IN1-: C13.2, R17.2, U4.3 (AIN1-)
/ADC_AD777x/ADC_IN2+: C14.1, R18.2, U4.10 (AIN2+)
/ADC_AD777x/ADC_IN2-: C14.2, R19.2, U4.9 (AIN2-)
/ADC_AD777x/ADC_IN3+: C15.1, R20.2, U4.12 (AIN3+)
/ADC_AD777x/ADC_IN3-: C15.2, R21.2, U4.11 (AIN3-)
/ADC_AD777x/ADC_IN4+: C16.1, R22.2, U4.47 (AIN4+)
/ADC_AD777x/ADC_IN4-: C16.2, R23.2, U4.48 (AIN4-)
/ADC_AD777x/ADC_IN5+: C17.1, R24.2, U4.45 (AIN5+)
/ADC_AD777x/ADC_IN5-: C17.2, R25.2, U4.46 (AIN5-)
/ADC_AD777x/ADC_IN6+: C18.1, R26.2, U4.39 (AIN6+)
/ADC_AD777x/ADC_IN6-: C18.2, R27.2, U4.40 (AIN6-)
/ADC_AD777x/ADC_IN7+: C19.1, R28.2, U4.37 (AIN7+)
/ADC_AD777x/ADC_IN7-: C19.2, R29.2, U4.38 (AIN7-)
/ADC_AD777x/ADC_MCLK: U4.32 (XTAL2/MCLK), Y1.3 (OUT)
/ADC_AD777x/ADC_MCLK_EN: R38.2, Y1.1 (Tri-State); also elsewhere on the board
/ADC_AD777x/ADC_REF+: C4.1, C6.1, C7.1, R13.1, U4.8 (REF1+), U4.41 (REF2+)
/ADC_AD777x/ADC_REF_OUT: C9.1, R13.2, U4.49 (REF_OUT)
/ADC_AD777x/ADC_RESET: R32.2, U4.36 (~RESET); also elsewhere on the board
/ADC_AD777x/ADC_SCLK: U4.19 (DCLK2/SCLK); also elsewhere on the board
/ADC_AD777x/ADC_SDI: U4.20 (DCLK1/SDI); also elsewhere on the board
/ADC_AD777x/ADC_SDO: R33.2; also elsewhere on the board
/ADC_AD777x/ADC_SDO_R: R33.1, U4.21 (DCLK0/SDO)
/ADC_AD777x/ADC_START: R31.1, U4.33 (~START); also elsewhere on the board
/ADC_AD777x/AIN0+: R14.1; also elsewhere on the board
/ADC_AD777x/AIN0-: R15.1; also elsewhere on the board
/ADC_AD777x/AIN1+: R16.1; also elsewhere on the board
/ADC_AD777x/AIN1-: R17.1; also elsewhere on the board
/ADC_AD777x/AIN2+: R18.1; also elsewhere on the board
/ADC_AD777x/AIN2-: R19.1; also elsewhere on the board
/ADC_AD777x/AIN4+: R22.1; also elsewhere on the board
/ADC_AD777x/AIN4-: R23.1; also elsewhere on the board
/ADC_AD777x/AIN5+: R24.1; also elsewhere on the board
/ADC_AD777x/AIN5-: R25.1; also elsewhere on the board
/ADC_AD777x/AIN6+: R26.1; also elsewhere on the board
/ADC_AD777x/AIN6-: R27.1; also elsewhere on the board
/ADC_AD777x/TH1+: R20.1; also elsewhere on the board
/ADC_AD777x/TH1-: R21.1; also elsewhere on the board
/ADC_AD777x/TH2+: R28.1; also elsewhere on the board
/ADC_AD777x/TH2-: R29.1; also elsewhere on the board
GND: C4.2, C5.2, C6.2, C7.2, C8.2, C9.2, C10.2, C11.2, C20.2, C21.2, C22.2, C23.2, C24.2, C25.2, C26.2, C27.2, C28.2, R30.2, R31.2, R37.2, U4.5 (AVSS1A), U4.7 (REF1-), U4.22 (DGND), U4.31 (XTAL1), U4.42 (REF2-), U4.44 (AVSS1B), U4.50 (AVSS2B), U4.53 (AVSS3), U4.56 (CLK_SEL), U4.60 (AVSS2A), U4.61 (AVSS4), U4.64 (AUXAIN-), U4.65 (EPAD(AVSSx)), Y1.2 (GND); also elsewhere on the board
unnamed: U4.34 (~SYNC_OUT), U4.35 (~SYNC_IN)

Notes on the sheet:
Vérifier clock specks vs température
